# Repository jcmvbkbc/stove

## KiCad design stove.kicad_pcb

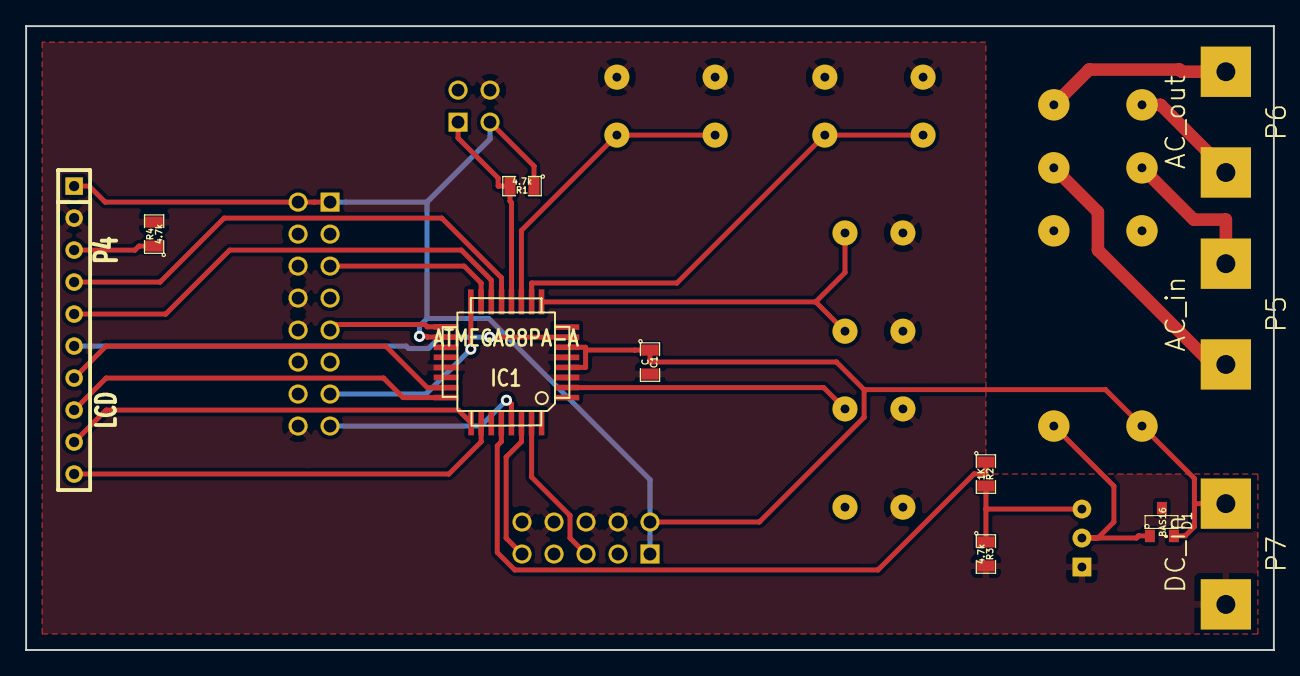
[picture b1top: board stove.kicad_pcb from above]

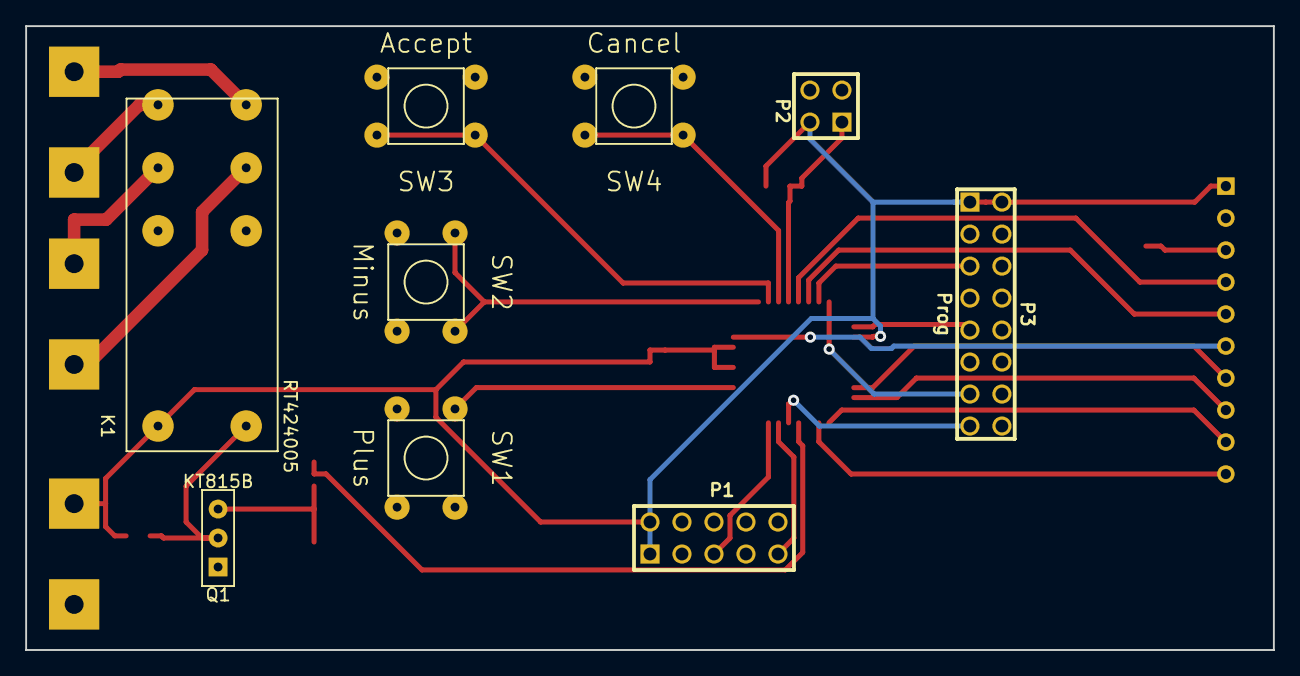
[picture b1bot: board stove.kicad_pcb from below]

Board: 2 copper layers, 99.1 x 49.5 mm, 20 parts (9 on the bottom side), 28 nets.

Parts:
C1: C; SM0805
D1: BAS16; SOT23
IC1: ATMEGA88PA-A; TQFP32
K1: RT424005
P1: Serial; PIN_ARRAY_5x2
P2: Thermo; PIN_ARRAY_2X2
P3: Prog; pin_array_8x2
P4: LCD; SIL-10
P5: AC_in; AC_CONN
P6: AC_out; AC_CONN
P7: DC_in; AC_CONN
Q1: KT815B; TO126
R1, R3, R4: 4.7k; SM0805
R2: 1K; SM0805
SW1: Plus; SW_TACT
SW2: Minus; SW_TACT
SW3: Accept; SW_TACT
SW4: Cancel; SW_TACT

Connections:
/AC_IN1: K1.5, P5.1
/AC_IN2: K1.12, P5.2
/AC_OUT1: K1.16, P6.1
/AC_OUT2: K1.1, P6.2
/LCD_D4: IC1.23, P4.7
/LCD_D5: IC1.24, P4.8
/LCD_D6: IC1.25, P4.9
/LCD_D7: IC1.26, P4.10
/LCD_E: IC1.7, P4.6
/LCD_RS: IC1.13, P4.4
/LCD_RW: IC1.14, P4.5
/RXD: IC1.30, P1.9
/SRST: IC1.29, P3.15
/SW_ACCEPT: IC1.10, SW3.1
/SW_CANCEL: IC1.11, SW4.1
/SW_MINUS: IC1.9, SW2.1
/SW_PLUS: IC1.2, SW1.1
/TCK: IC1.17, P3.9
/TDI: IC1.15, P3.5
/TDO: IC1.16, P3.13
/TXD: IC1.31, P1.5
GND: C1.2, IC1.3, IC1.5, IC1.21, P1.4, P1.6, P1.8, P1.10, P2.4, P3.4, P3.6, P3.8, P3.10, P3.12, P3.14, P3.16, P4.2, P7.2, Q1.1, R3.2, R4.2, SW1.2, SW2.2, SW3.2, SW4.2
unnamed: IC1.12, P2.1, R1.2
unnamed: IC1.28, R2.1
unnamed: D1.1, K1.9, Q1.2
unnamed: P4.3, R4.1
unnamed: Q1.3, R2.2, R3.1
VCC: C1.1, D1.2, IC1.4, IC1.6, IC1.18, K1.8, P1.1, P1.2, P2.2, P3.1, P3.2, P4.1, P7.1, R1.1

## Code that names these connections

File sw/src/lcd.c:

#include <avr/io.h>
#include <util/delay.h>
#include "lcd.h"

#define LCD_CTRL_DDR	DDRB
#define LCD_CTRL_PORT	PORTB
#define LCD_RS		_BV(PB1)
#define LCD_RW		_BV(PB2)
#define LCD_E		_BV(PB6)
#define LCD_CTRL_MASK	(LCD_RS | LCD_RW | LCD_E)

#define LCD_DATA_DDR	DDRC
#define LCD_DATA_PORT	PORTC
#define LCD_DATA_SHIFT	0
#define LCD_DATA_MASK	0xf

static uint8_t lcd_addr;
static uint8_t lcd_current_page;

static inline void lcd_prepare_write(uint8_t addr)
{
	LCD_CTRL_PORT = (LCD_CTRL_PORT & ~LCD_CTRL_MASK) |
		((addr & 1) ? LCD_RS : 0);
	LCD_DATA_DDR |= LCD_DATA_MASK;
	_delay_us(1);
}

static void lcd_write_nibble(uint8_t v)
{
	LCD_CTRL_PORT |= LCD_E;
	LCD_DATA_PORT &= ~LCD_DATA_MASK;
	LCD_DATA_PORT |= (v << LCD_DATA_SHIFT) & LCD_DATA_MASK;
	_delay_us(1);
	LCD_CTRL_PORT &= ~LCD_E;
	_delay_us(1);
}

static void lcd_write(uint8_t addr, uint8_t v)
{
	lcd_prepare_write(addr);
	lcd_write_nibble(v >> 4);
	lcd_write_nibble(v);
}

void lcd_clear(void)
{
	lcd_write(0, 1);
	_delay_ms(2);
	lcd_addr = 0;
}

void lcd_on(uint8_t mode)
{
	lcd_write(0, 0x8 | (mode & 7));
	_delay_us(40);
}

void lcd_set_entry_mode(uint8_t mode)
{
	lcd_write(0, 0x4 | (mode & 3));
	_delay_us(40);
}

static inline void lcd_set_addr(uint8_t addr)
{
	lcd_addr = addr & LCD_ADDR_MASK;
	lcd_write(0, 0x80 | lcd_addr);
	_delay_us(40);
}

static void lcd_init_hints(void)
{
	static const uint8_t cg[] = {
		0x0, 0x2, 0x0, 0x2, 0x0, 0xa, 0x0, 0x0, /* all */
		0x0, 0x2, 0x0, 0x2, 0x0, 0x2, 0x0, 0x0, /* +/-/accept */
		0x0, 0x0, 0x0, 0x0, 0x0, 0xa, 0x0, 0x0, /* accept/cancel */

	};
	uint8_t i;

	lcd_write(0, 0x40);
	_delay_us(40);
	for (i = 0; i < sizeof(cg); ++i) {
		lcd_write(1, cg[i]);
		_delay_us(40);
	}
}

void lcd_init(void)
{
	LCD_CTRL_PORT &= ~LCD_CTRL_MASK;
	LCD_CTRL_DDR |= LCD_CTRL_MASK;

	_delay_ms(20);
	lcd_prepare_write(0);
	lcd_write_nibble(0x3);
	_delay_us(40);
	lcd_write_nibble(0x3);
	_delay_us(40);
	lcd_write_nibble(0x3);
	_delay_us(40);
	lcd_write_nibble(0x2);
	_delay_us(40);
	lcd_write(0, 0x28);
	_delay_us(40);
	lcd_on(0);
	lcd_clear();
	lcd_set_entry_mode(LCD_MODE_ID);
	lcd_on(LCD_ON_DISPLAY | LCD_ON_BLINK);
	lcd_init_hints();
}

void lcd_xy(uint8_t x, uint8_t y)
{
	lcd_set_addr((x & (LCD_STRIDE - 1)) + LCD_STRIDE * y);
}

void lcd_putc(char c)
{
	lcd_write(1, c);
	_delay_us(40);
	lcd_addr = (lcd_addr + 1) & LCD_ADDR_MASK;
}

void lcd_puts(const char *str)
{
	uint8_t x = lcd_addr & (LCD_STRIDE - 1);

	for (; x < LCD_STRIDE && *str; ++x, ++str) {
		lcd_putc(*str);
	}
}

void lcd_puts_xy(uint8_t x, uint8_t y, const char *str)
{
	for (lcd_xy(x, y); x < LCD_STRIDE && *str; ++x, ++str) {
		lcd_putc(*str);
	}
}

static void lcd_shift(uint8_t shift)
{
	lcd_write(0, 0x10 | (shift & 0xc));
	_delay_us(40);
}

void lcd_page(uint8_t page)
{
	uint8_t shift = LCD_SHIFT_SC;
	uint8_t d;
	uint8_t i;

	if (page < lcd_current_page) {
		shift |= LCD_SHIFT_RL;
		d = lcd_current_page - page;
	} else {
		d = page - lcd_current_page;
	}
	for (i = 0; i < d * 16; ++i) {
		lcd_shift(shift);
	}
	lcd_current_page = page;
}

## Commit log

2013-11-16 initial
2013-11-17 add small size PCB
2013-11-26 Move HW part to hw/
2013-11-26 sw: add makefile and simple main
2013-12-07 sw: fix programmer settings, enable debug
2013-12-07 sw: switch to delay_basic, fix thermometer input
2013-12-07 sw: add UART
2013-12-07 sw: add temperature measurement
2013-12-08 sw: extract owi_read_bit, fix waiting for T conversion completion
2013-12-08 sw: remove eeprom debug from owi
2013-12-08 sw: switch owi port while owi ddr is cleared (in)
2013-12-08 sw: get rid of get_t float return value
    Float here makes little sense since we don't really need that precision.
    Also 0.5, 0.25, 0.125 and 0.0625 are actually 1/2, 1/4, 1/8 and 1/16.
2013-12-08 sw: improve owi_init
    Detect not only presence pulse by slave, but also bus release after
    initialization.
2013-12-08 sw: fix owi_write timing
    With these changes we get correct timing that OWI slave does understand.
    Also always release bus after write completion.
2013-12-11 sw: use fixed point (4 fractional bits) for temperature
2013-12-11 sw: fix infinite loop on failure to complete temp conversion
2013-12-11 sw: implement simple thermostat
2013-12-16 sw: add UART indication
2013-12-17 sw: add LCD support
2013-12-17 sw: add version string
2013-12-17 sw: add keys support
2013-12-19 sw: fix lcd initialization
2013-12-26 sw: display current temperature on LCD
2013-12-26 sw: add keys IRQ handling
2013-12-26 sw: add irq flags save/restore functions
2013-12-26 sw: fix eeprom write, add eeprom read
2013-12-26 sw: update fixed thermostat range
2013-12-26 sw: rearrange initialization sequence
2013-12-27 sw: added timer in ms
2013-12-27 sw: make OWI asynchronous and IRQ-safe
2014-01-01 sw: move eeprom functions to separate file
2014-01-02 sw: add core state save/load
2014-01-03 sw: rename get_ms to timer_get_time
2014-01-03 sw: add generic purpose timers
2014-01-03 sw: move keys to separate file
2014-01-03 sw: move interrupt related code to separate file
2014-01-03 sw: move uart to separate file
2014-01-03 sw: move heater to separate file
2014-01-03 sw: switch to asynchronous operation
2014-01-04 sw: add timer_set_time
2014-01-04 sw: move ui functions to separate file
2014-01-04 sw: move thermometer maintenance to separate file
2014-01-04 sw: fix state crc checking
2014-01-04 sw: introduce stove_state
2014-01-04 sw: move thermostat to separate file
2014-01-04 sw: load and save state periodically
2014-01-04 sw: extract thermostat UI update
2014-01-04 sw: add thermostat keyboard handler
2014-01-04 sw: change cursor shape to block
2014-01-04 sw: fix stale thermostat time display
2014-01-05 sw: move eeprom base addresses to eeprom.h
2014-01-05 sw: set up osccal on startup
2014-01-05 sw: add lcd hint display
2014-01-05 sw: display hint on thermostat view
2014-01-05 sw: switch to 8MHz
2014-01-05 sw: add LCD page selection
2014-01-06 sw: add progs and points per prog limits
2014-01-06 sw: add menu
2014-01-06 sw: add prog thermostat
2014-01-06 sw: allow editing current time, restrict editors by mode
